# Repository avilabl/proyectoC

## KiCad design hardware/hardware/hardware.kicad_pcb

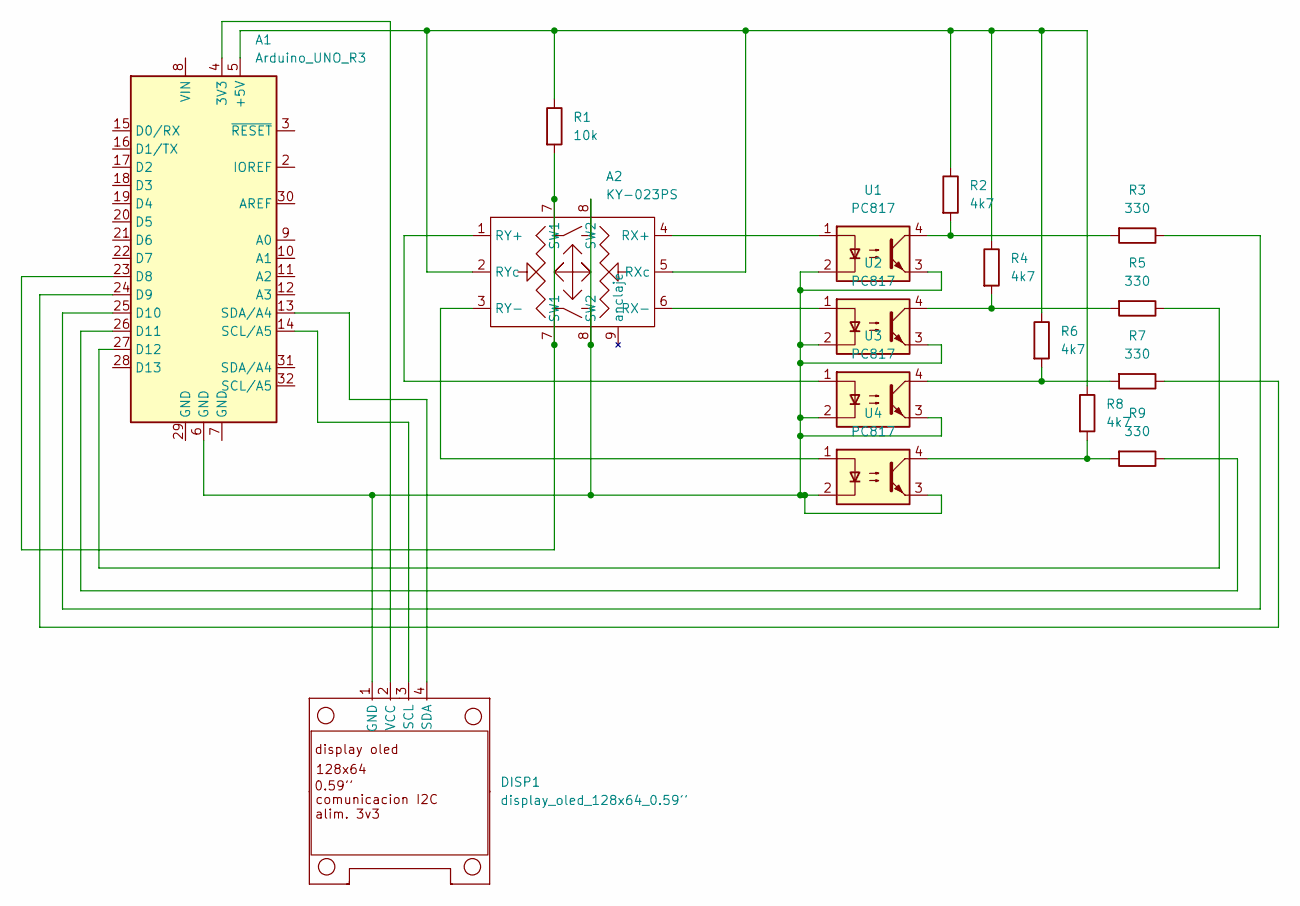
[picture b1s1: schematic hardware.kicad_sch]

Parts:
A1: Arduino_UNO_R3
A2: KY-023PS; KY023-joystickPS
DISP1: display_oled_128x64_0.59''; Display_oled_128x64_0.59''
R1: 10k; R_Axial_DIN0204_L3.6mm_D1.6mm_P7.62mm_Horizontal
R2, R4, R6, R8: 4k7; R_Axial_DIN0204_L3.6mm_D1.6mm_P7.62mm_Horizontal
R3, R5, R7, R9: 330; R_Axial_DIN0204_L3.6mm_D1.6mm_P7.62mm_Horizontal
U1, U2, U3, U4: PC817; DIP-4_W7.62mm

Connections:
unnamed: A1.4 (3V3), DISP1.2 (VCC)
unnamed: A1.5 (+5V), A2.2 (RYc), A2.5 (RXc), R1.1, R2.1, R4.1, R6.1, R8.1
unnamed: A1.6 (GND), A2.8 (SW2), DISP1.1 (GND), U1.2, U1.3, U2.2, U2.3, U3.2, U3.3, U4.2, U4.3
unnamed: A1.13 (SDA/A4), DISP1.4 (SDA)
unnamed: A1.14 (SCL/A5), DISP1.3 (SCL)
unnamed: A1.23 (D8), A2.7 (SW1), R1.2
unnamed: A1.24 (D9), R7.1
unnamed: A1.25 (D10), R3.1
unnamed: A1.26 (D11), R9.1
unnamed: A1.27 (D12), R5.1
unnamed: A2.1 (RY+), U3.1
unnamed: A2.3 (RY-), U4.1
unnamed: A2.4 (RX+), U1.1
unnamed: A2.6 (RX-), U2.1
unnamed: R2.2, R3.2, U1.4
unnamed: R4.2, R5.2, U2.4
unnamed: R6.2, R7.2, U3.4
unnamed: R8.2, R9.2, U4.4

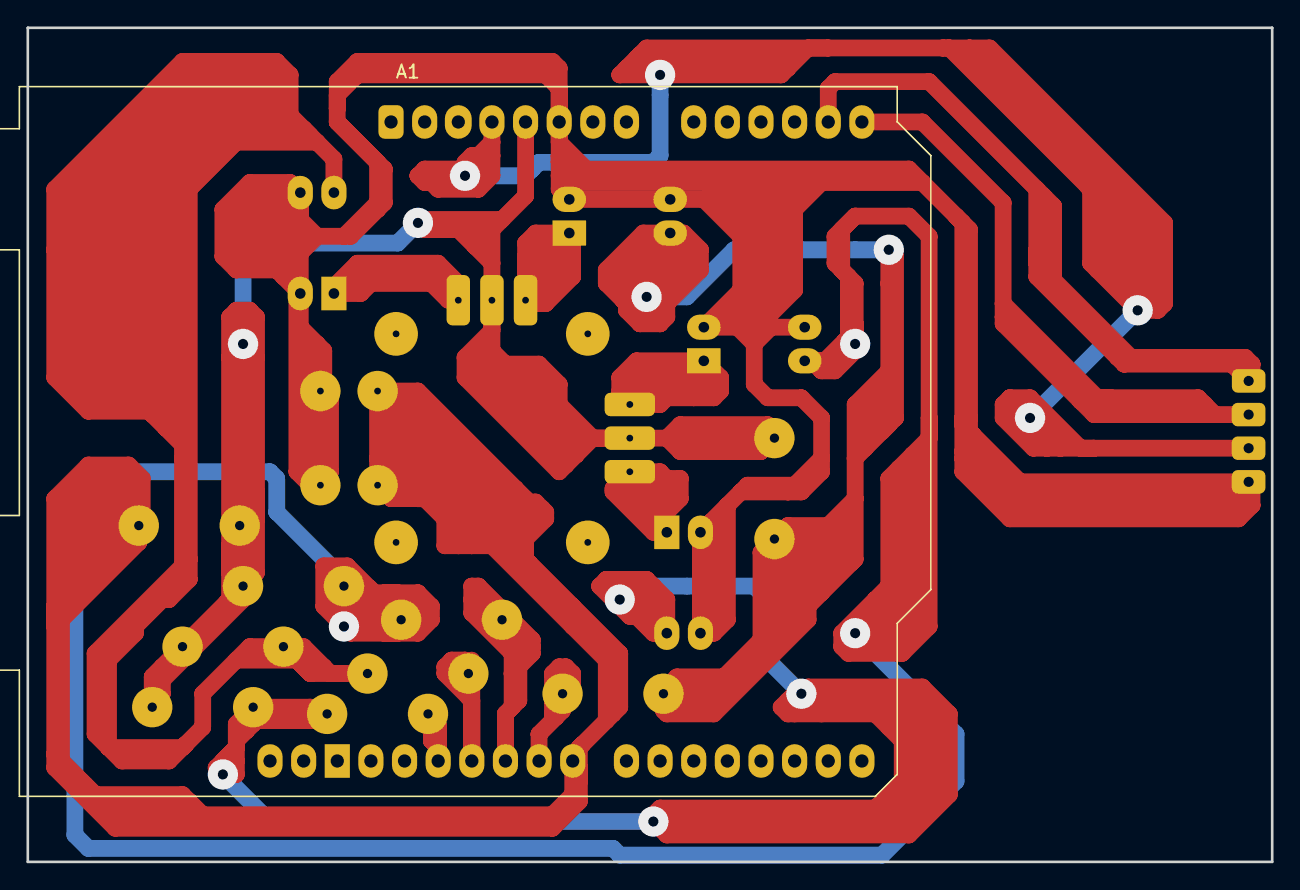
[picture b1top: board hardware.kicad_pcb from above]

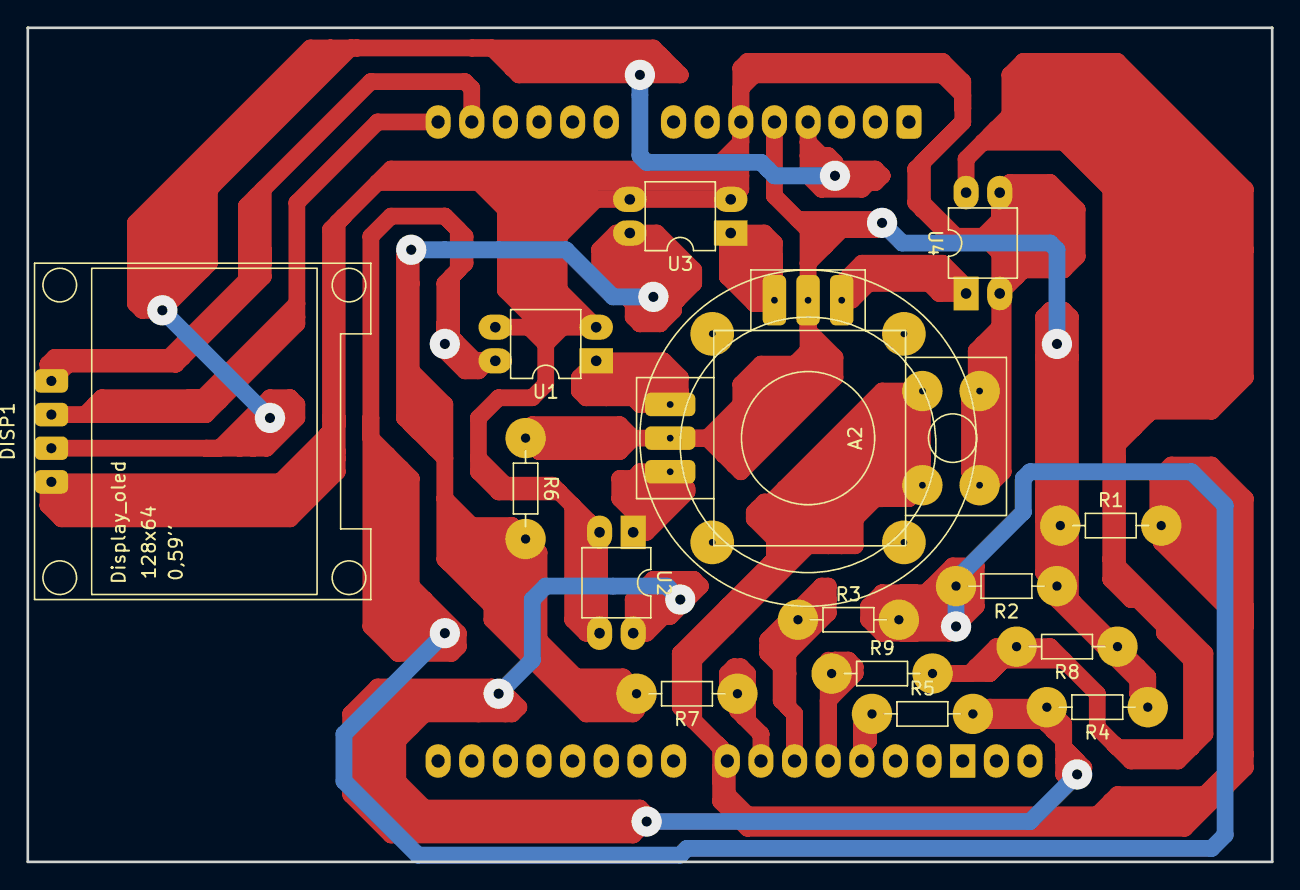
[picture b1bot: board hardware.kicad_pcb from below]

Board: 2 copper layers, 94.0 x 63.0 mm, 16 parts (15 on the bottom side), 18 nets.

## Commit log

2024-05-17 primer comit con menu resuelto
2024-05-24 se agrego la carpeta de hardware y estan la libreria de cada juego y se esta trabajando en el juego snake
2024-05-27 todo el movimiento de la viborita hecho y la comiday captura..falta modificar velocidad pausa y guardado de max score
2024-05-31 solucionado problema que se paraba la viborita
